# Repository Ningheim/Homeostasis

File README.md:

# Homeostasis
A smart laptop cooling stand!

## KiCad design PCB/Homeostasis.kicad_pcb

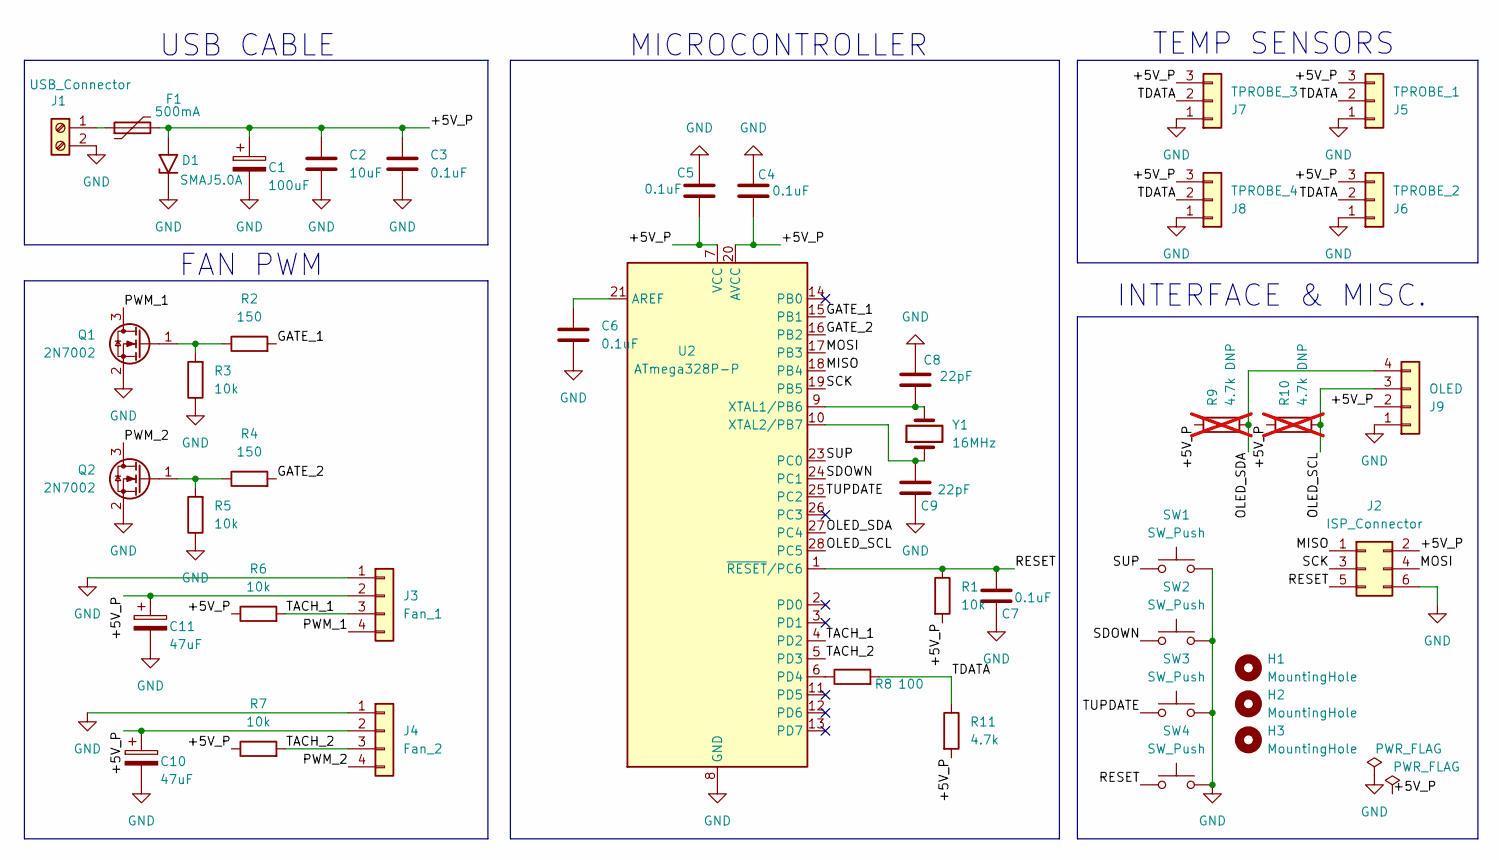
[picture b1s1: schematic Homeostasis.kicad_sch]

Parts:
C1: 100uF; CP_Radial_D6.3mm_P2.50mm
C2: 10uF; C_1206_3216Metric
C3, C4, C5, C6, C7: 0.1uF; C_0805_2012Metric
C8: 22pF; C_0805_2012Metric
C9: 22pF; C_0805_2012Metric_Pad1.18x1.45mm_HandSolder
C10, C11: 47uF; CP_Radial_D5.0mm_P2.00mm
D1: SMAJ5.0A; D_SMA
F1: 500mA; Fuse_1206_3216Metric_Pad1.42x1.75mm_HandSolder
H1, H2, H3: MountingHole; MountingHole_3.2mm_M3
J1: USB_Connector; TerminalBlock_Phoenix_MKDS-1,5-2_1x02_P5.00mm_Horizontal
J2: ISP_Connector; PinHeader_2x03_P2.54mm_Vertical
J3: Fan_1; Molex_KK-254_AE-6410-04A_1x04_P2.54mm_Vertical
J4: Fan_2; Molex_KK-254_AE-6410-04A_1x04_P2.54mm_Vertical
J5: TPROBE_1; JST_XH_B3B-XH-A_1x03_P2.50mm_Vertical
J6: TPROBE_2; JST_XH_B3B-XH-A_1x03_P2.50mm_Vertical
J7: TPROBE_3; JST_XH_B3B-XH-A_1x03_P2.50mm_Vertical
J8: TPROBE_4; JST_XH_B3B-XH-A_1x03_P2.50mm_Vertical
J9: OLED; PinSocket_1x04_P2.54mm_Vertical
Q1, Q2: 2N7002; SOT-23
R1, R3, R5, R6, R7: 10k; R_0805_2012Metric
R2, R4: 150; R_0805_2012Metric
R8: 100; R_0805_2012Metric
R9, R10: 4.7k DNP; R_0805_2012Metric; not fitted
R11: 4.7k; R_0805_2012Metric
SW1, SW2, SW3, SW4: SW_Push; SW_PUSH_6mm_H5mm
U2: ATmega328P-P; DIP-28_W7.62mm
Y1: 16MHz; Crystal_HC49-U_Vertical

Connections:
/+5V_P: C1.1, C2.1, C3.1, C4.2, C5.2, C10.1, C11.1, D1.2 (A2), F1.2, J2.2, J3.2, J4.2, J5.3, J6.3, J7.3, J8.3, J9.2, R1.2, R6.1, R7.1, R9.1, R10.1, R11.2, U2.7 (VCC), U2.20 (AVCC)
/GATE_1: R2.2, U2.15 (PB1)
/GATE_2: R4.2, U2.16 (PB2)
/MISO: J2.1, U2.18 (PB4)
/MOSI: J2.4, U2.17 (PB3)
/OLED_SCL: J9.3, R10.2, U2.28 (PC5)
/OLED_SDA: J9.4, R9.2, U2.27 (PC4)
/PWM_1: J3.4, Q1.3 (D)
/PWM_2: J4.4, Q2.3 (D)
/RESET: C7.2, J2.5, R1.1, SW4.1, U2.1 (~RESET/PC6)
/SCK: J2.3, U2.19 (PB5)
/SDOWN: SW2.1, U2.24 (PC1)
/SUP: SW1.1, U2.23 (PC0)
/TACH_1: J3.3, R6.2, U2.4 (PD2)
/TACH_2: J4.3, R7.2, U2.5 (PD3)
/TDATA: J5.2, J6.2, J7.2, J8.2, R8.2, R11.1
/TUPDATE: SW3.1, U2.25 (PC2)
GND: C1.2, C2.2, C3.2, C4.1, C5.1, C6.1, C7.1, C8.1, C9.1, C10.2, C11.2, D1.1 (A1), J1.2, J2.6, J3.1, J4.1, J5.1, J6.1, J7.1, J8.1, J9.1, Q1.2 (S), Q2.2 (S), R3.1, R5.1, SW1.2, SW2.2, SW3.2, SW4.2, U2.8 (GND), U2.22 (GND)
unnamed: F1.1, J1.1
unnamed: Q1.1 (G), R2.1, R3.2
unnamed: Q2.1 (G), R4.1, R5.2
unnamed: C6.2, U2.21 (AREF)
unnamed: R8.1, U2.6 (PD4)
unnamed: C8.2, U2.9 (XTAL1/PB6), Y1.2
unnamed: C9.2, U2.10 (XTAL2/PB7), Y1.1

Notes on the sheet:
FAN PWM
INTERFACE & MISC.
MICROCONTROLLER
USB CABLE
TEMP SENSORS

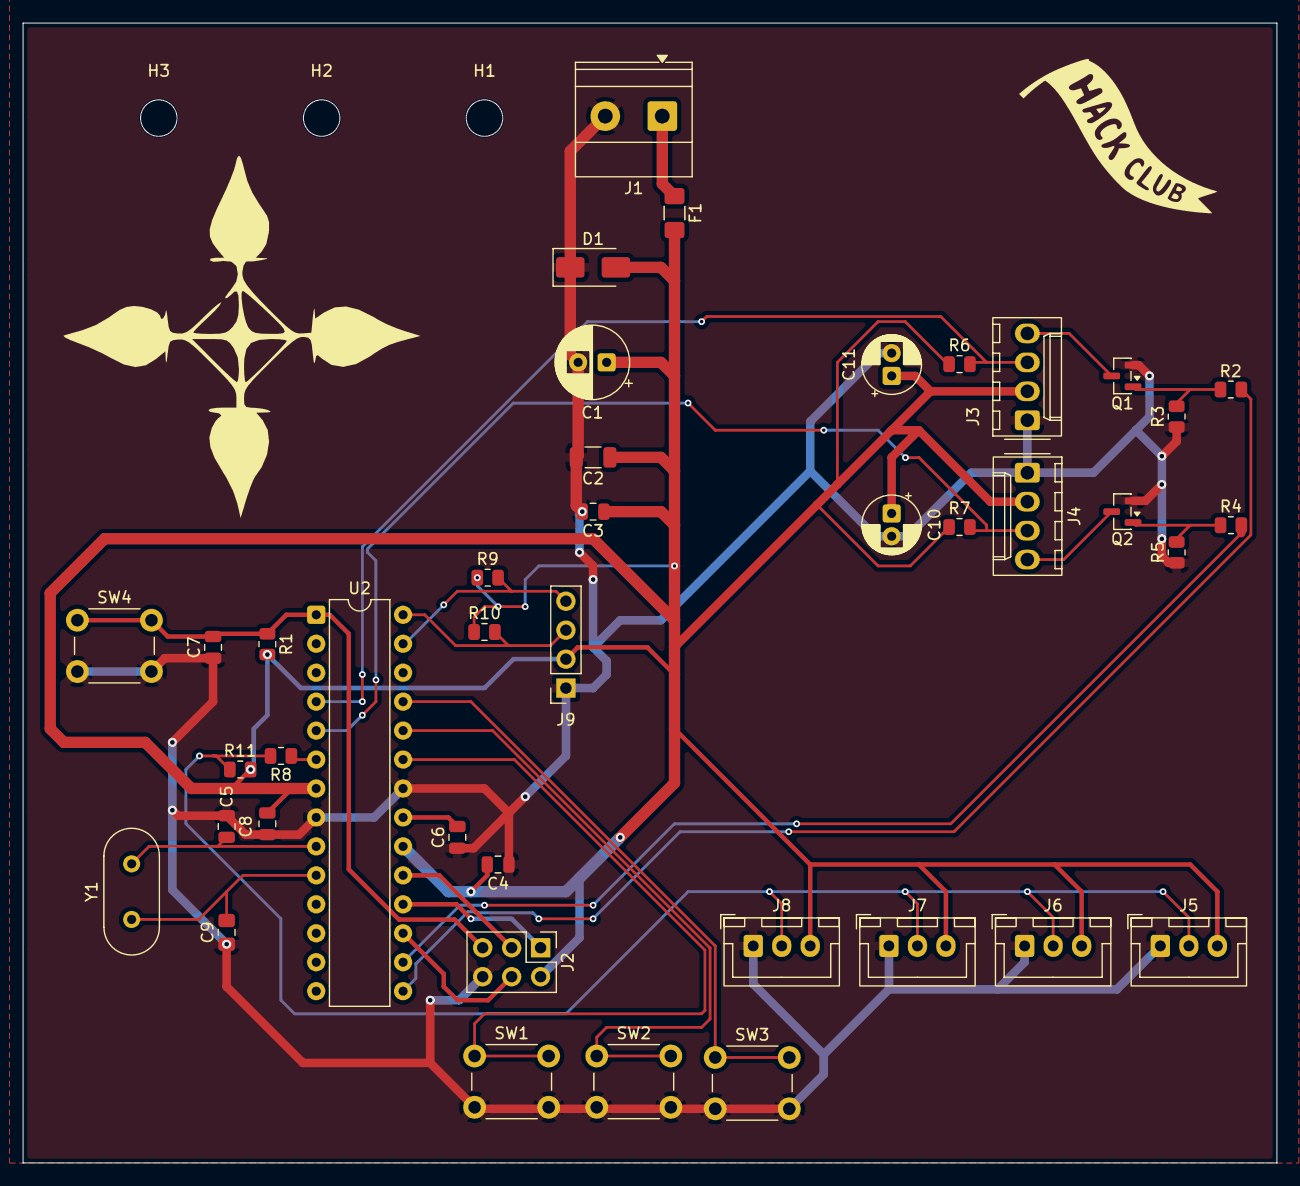
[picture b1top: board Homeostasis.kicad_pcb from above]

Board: 2 copper layers, 110.0 x 100.0 mm, 44 parts (0 on the bottom side), 25 nets.

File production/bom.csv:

Designator,Footprint,Quantity,Value,LCSC Part #
,462f2333-586c-4cc8-b04d-9995b911b9d8,1,,
C1,CP_Radial_D6.3mm_P2.50mm,1,100uF,
"C10, C11",CP_Radial_D5.0mm_P2.00mm,2,47uF,
C2,1206,1,10uF,
"C3, C4, C5, C6, C7",0805,5,0.1uF,
"C8, C9",0805,2,22pF,
D1,D_SMA,1,SMAJ5.0A,
F1,1206,1,500mA,
J1,"TerminalBlock_Phoenix_MKDS-1,5-2_1x02_P5.00mm_Horizontal",1,USB_Connector,
J2,PinHeader_2x03_P2.54mm_Vertical,1,ISP_Connector,
J3,Molex_KK-254_AE-6410-04A_1x04_P2.54mm_Vertical,1,Fan_1,
J4,Molex_KK-254_AE-6410-04A_1x04_P2.54mm_Vertical,1,Fan_2,
J5,JST_XH_B3B-XH-A_1x03_P2.50mm_Vertical,1,TPROBE_1,
J6,JST_XH_B3B-XH-A_1x03_P2.50mm_Vertical,1,TPROBE_2,
J7,JST_XH_B3B-XH-A_1x03_P2.50mm_Vertical,1,TPROBE_3,
J8,JST_XH_B3B-XH-A_1x03_P2.50mm_Vertical,1,TPROBE_4,
J9,PinSocket_1x04_P2.54mm_Vertical,1,OLED,
"Q1, Q2",SOT-23,2,2N7002,
"R1, R3, R5, R6, R7",0805,5,10k,
"R10, R9",0805,2,4.7k DNP,
R11,0805,1,4.7k,
"R2, R4",0805,2,150,
R8,0805,1,100,
"SW1, SW2, SW3, SW4",SW_PUSH_6mm_H5mm,4,SW_Push,
U2,DIP-28_W7.62mm,1,ATmega328P-P,
Y1,Crystal_HC49-U_Vertical,1,16MHz,
